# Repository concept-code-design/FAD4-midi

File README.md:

# FAD4-midi

Fad 4 is a USB MIDI controller with 4 faders

The device sports a USB type-C connector and requires no device drivers on Mac or PC.

The faders (slider potentiometers) can be configured (via MIDI messages, or the configurator) to produce CC codes.
The device uses a modified midi library for CH55x devices made by mi:muz 

## Configuring the sliders
Configuration is easy with midiutil.py

start prog
./midiutil.py -d 1 -w 186 102 42
returns [185, 102, 42]

end prog
./midiutil.py -d 1 -w 186 102 43

get module type
./midiutil.py -d 1 -w 186 102 44
returns: (10, 103, INSTRUMENT_TYPE);

get firmware version
./midiutil.py -d 1 -w 186 102 45
returns (10, 104, FW_VERSION) 10 for version 1.0

show configuration
./midiutil.py -d 1 -w 186 102 46
returns the config of each of the 4 sliders

set MIDI channel 
./midiutil.py -d 1 -w 186 102 48
returns (10, 106, MIDIChannel)

reboot in firmware update mode
./midiutil.py -d 1 -w 186 102 49

programming sliders
./midiutil.py -d 1 -w 186 102 42

./midiutil.py -d 1 -w 186 1 9

./midiutil.py -d 1 -w 186 2 15

./midiutil.py -d 1 -w 186 3 21

./midiutil.py -d 1 -w 186 4 22

./midiutil.py -d 1 -w 186 102 43

sets slider 1 to CC 9, 2 to 15 etc

## Links & References

* [mi:muz:ch55x Tiny USB MIDI Library for Ch55xduino](https://github.com/mimuz/mimuz-ch55x)
* [python-rtmidi](http://pypi.python.org/pypi/python-rtmidi/)
* [midiutil](https://github.com/sourcebox/midiutil)

# License

Concept & Code invests time and resources providing this open source design, please support them and open-source hardware by purchasing products from Etsy or Tindie!

Designed by Ronald Leenes.

Firmware released under an GNU AGPL v3.0 license. See the LICENSE file for more information.

Hardware released under an CERN Open Hardware Licence v1.2. See the LICENSE_HARDWARE file for more information.

February 2025

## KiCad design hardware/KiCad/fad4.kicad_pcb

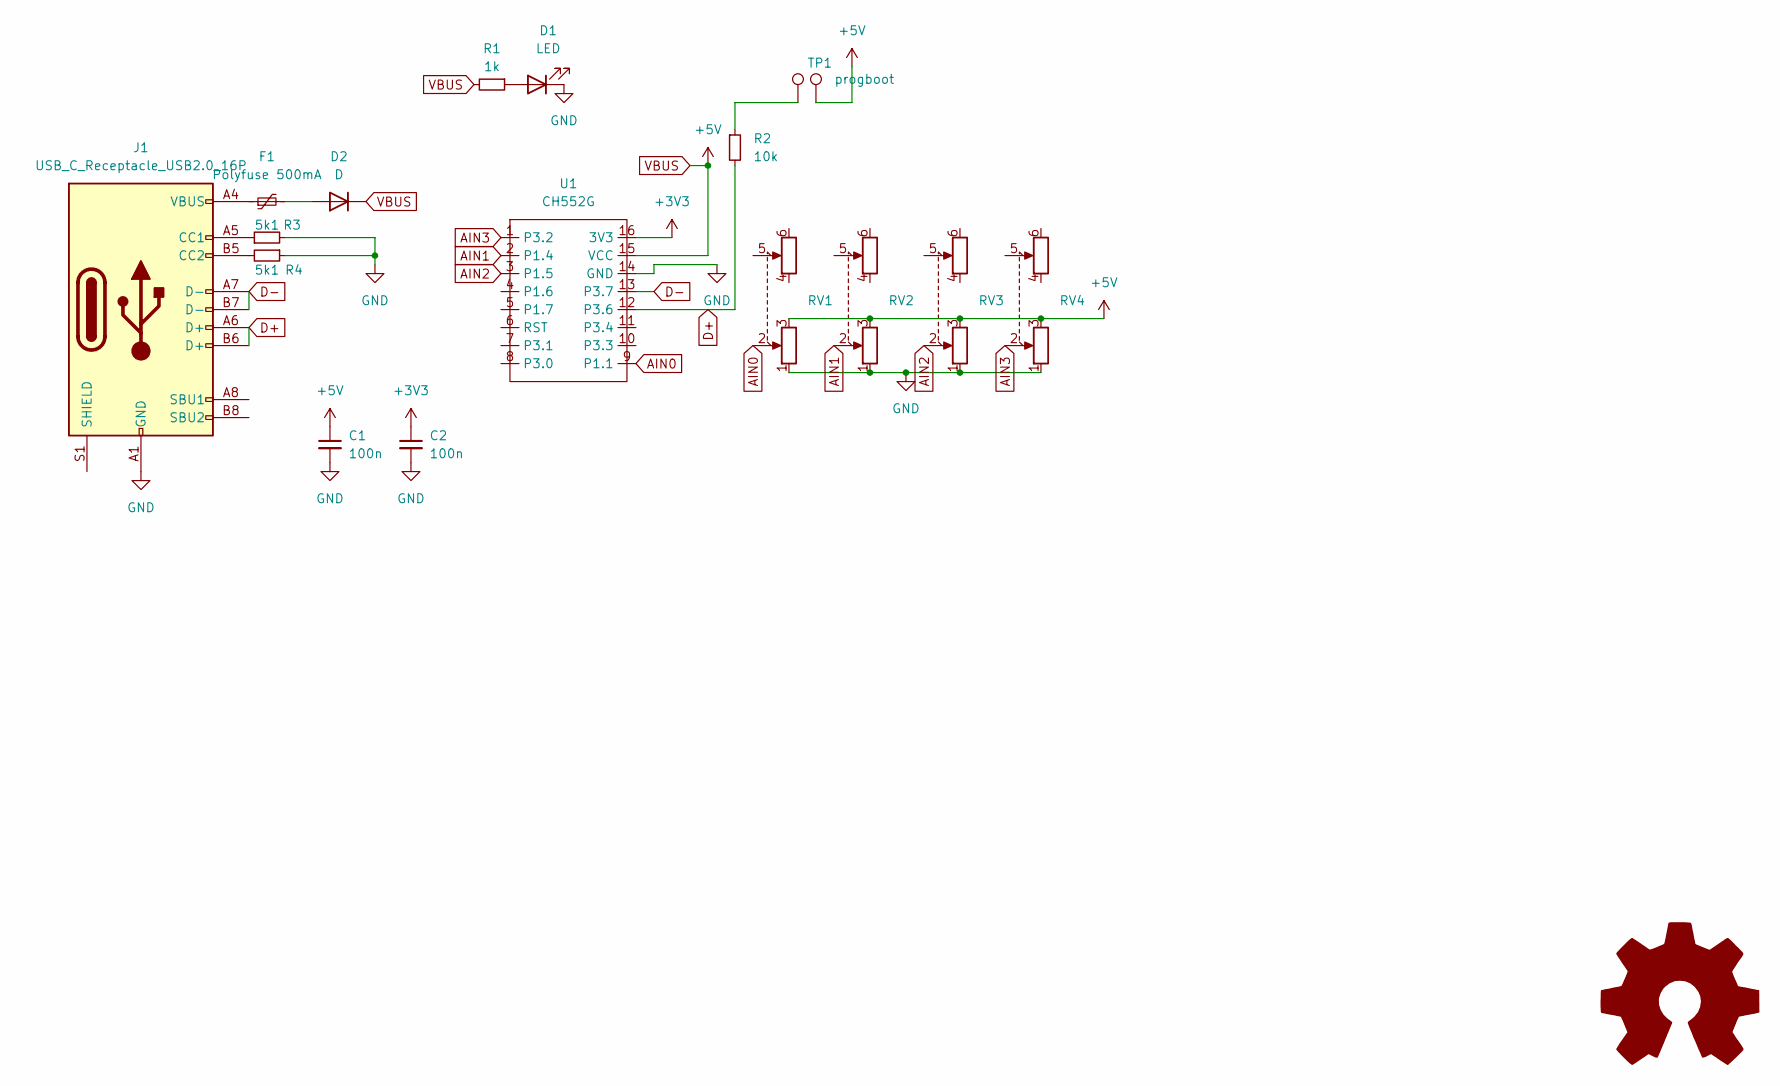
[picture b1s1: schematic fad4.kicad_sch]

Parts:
C1, C2: 100n; C_1206_3216Metric
D1: LED; LED_0603_1608Metric
D2: D; D_SMA_Handsoldering
F1: Polyfuse 500mA; Fuse_1210_3225Metric
J1: USB_C_Receptacle_USB2.0_16P; USB_C_Receptacle_GCT_USB4105-xx-A_16P_TopMnt_Horizontal
R1: 1k; R_1206_3216Metric
R2: 10k; R_1206_3216Metric
R3, R4: 5k1; R_1206_3216Metric
RV1, RV2, RV3, RV4: R_Potentiometer_Dual; B103 slider 4560mm
TP1, TP2: progboot; TestPoint_Pad_1.5x1.5mm
U1: CH552G

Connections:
+3V3: C2.1, U1.16 (3V3)
AIN0: RV1.2, U1.9 (P1.1)
AIN1: RV2.2, U1.2 (P1.4)
AIN2: RV3.2, U1.3 (P1.5)
AIN3: RV4.2, U1.1 (P3.2)
D+: J1.A6 (D+), J1.B6 (D+), R2.2, U1.12 (P3.6)
D-: J1.A7 (D-), J1.B7 (D-), U1.13 (P3.7)
GND: C1.2, C2.2, D1.1 (K), J1.A1 (GND), J1.A12 (GND), J1.B1 (GND), J1.B12 (GND), R3.2, R4.1, RV1.1, RV2.1, RV3.1, RV4.1, U1.14 (GND)
unnamed: D1.2 (A), R1.1
unnamed: D2.2 (A), F1.2
unnamed: F1.1, J1.A4 (VBUS), J1.A9 (VBUS), J1.B4 (VBUS), J1.B9 (VBUS)
unnamed: J1.A5 (CC1), R3.1
unnamed: J1.B5 (CC2), R4.2
unnamed: R2.1, TP1.1
VBUS: C1.1, D2.1 (K), R1.2, RV1.3, RV2.3, RV3.3, RV4.3, TP2.1, U1.15 (VCC)

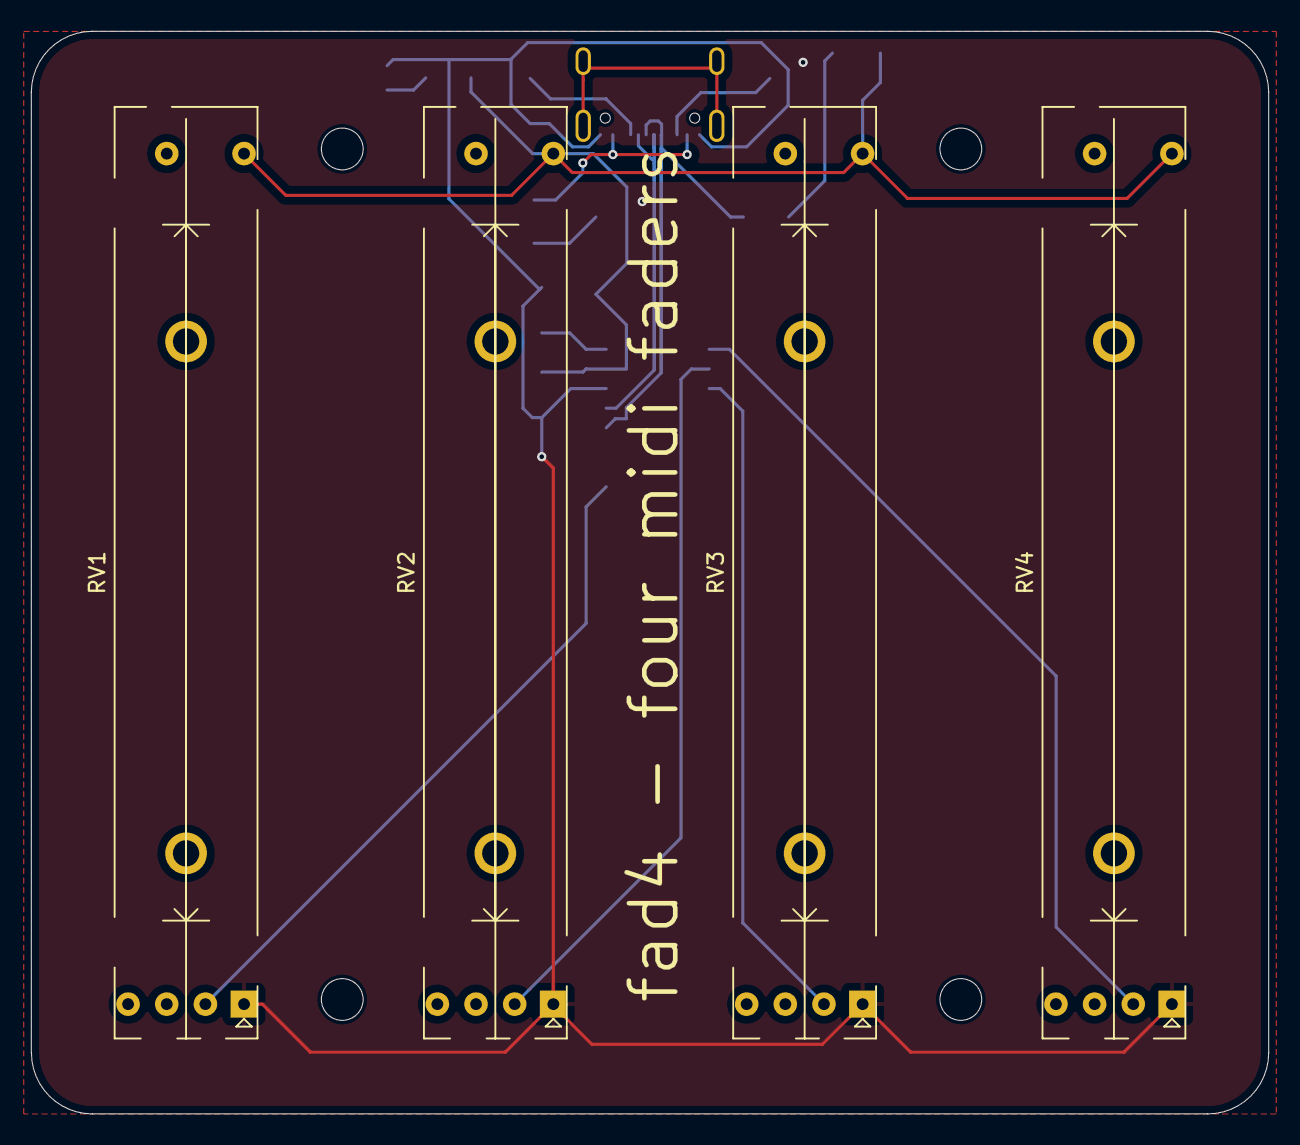
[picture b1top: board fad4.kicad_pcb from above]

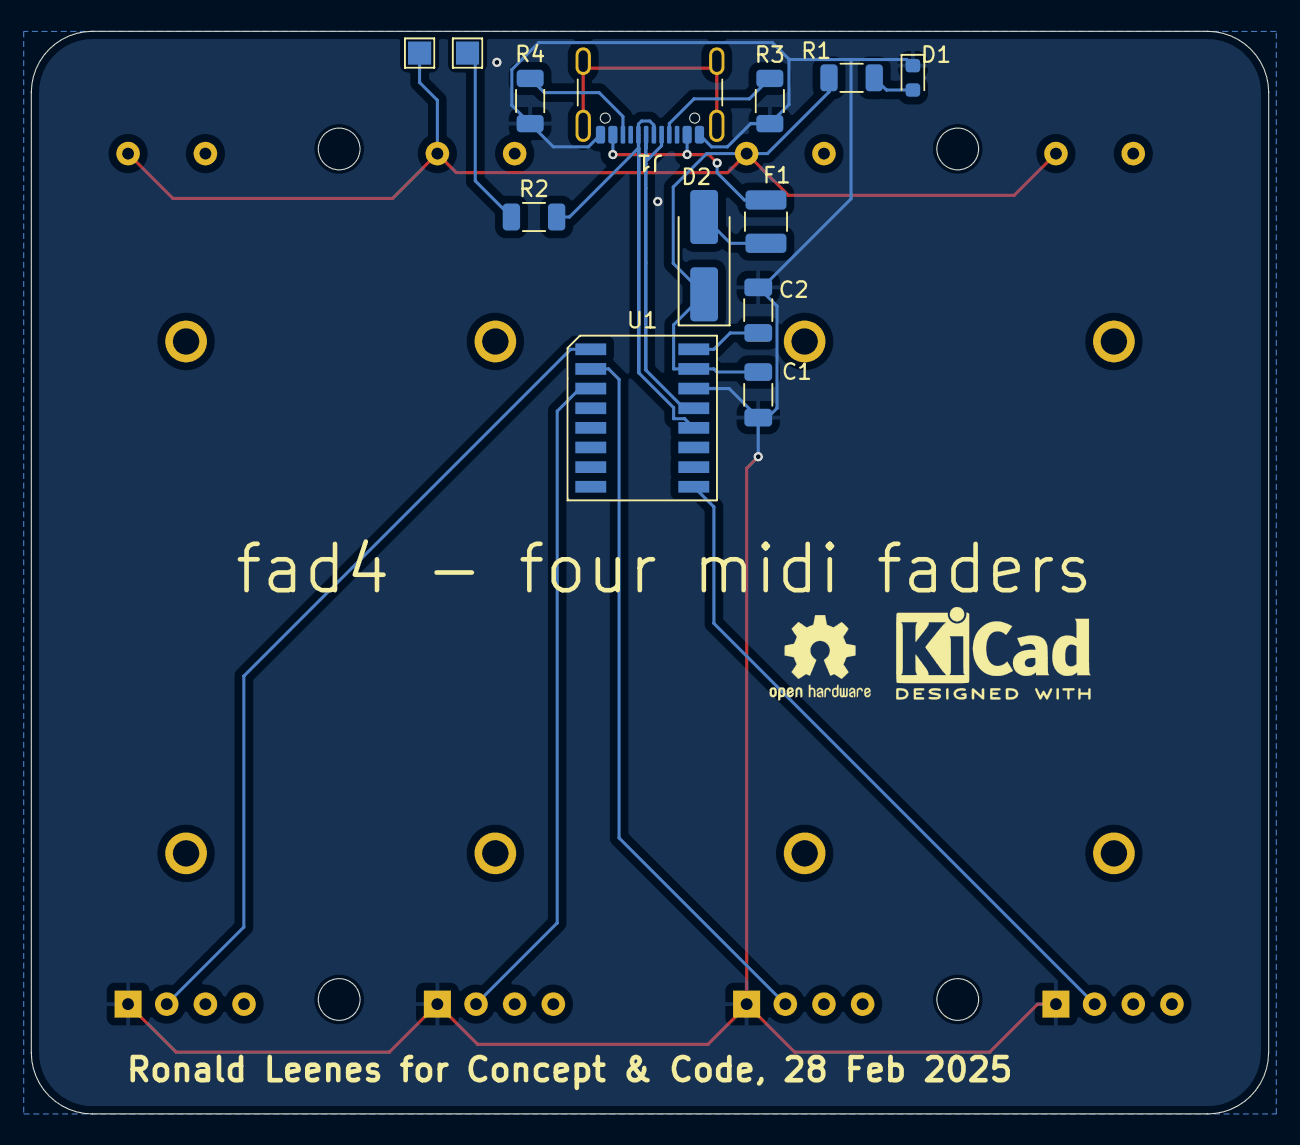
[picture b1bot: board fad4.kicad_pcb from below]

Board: 2 copper layers, 80.0 x 70.0 mm, 21 parts (13 on the bottom side), 15 nets.

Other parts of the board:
h1, h2, h3, h4: MountingHole_2.7mm_M2.5_DIN965

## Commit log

2025-02-28 firmware v1.0
2025-03-04 fixed 43 issue
2025-03-24 fixes
    fixes
2025-04-26 compiled binaries included
2025-05-14 Added KiCad files
